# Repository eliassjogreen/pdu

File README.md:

# 10" 1U PDU

A modular 10" 1U PDU which repurposes the common slot HP server power supplies.
It's designed around a single 12V rail supplied by the powerful and probably
overkill HP common slot power supplies. To supply downstream devices there are
internal XT60 connectors, which in turn are used to buck or boost the 12V rail
to desired voltages, for example 19V for common mini-pc's.

## Specifications

Depending on the [HP common slot power supply](https://support.hpe.com/hpesc/public/docDisplay?docId=c03502743)
you decide to get there is some variation in the capabilities of the PDU. I
have the 750W (DPS-750RB and HSTNS-PL18) variant of the supply outputting 12V
62.5A on the main rail, but also 12V 2.5A of standby power which is always on.
The PDU will probably work with the 1200W version, but because I designed it
with the 750W version in mind some connectors and the PCB might technically be
undersized for such loads. The smaller 460W version should work just fine still.

There are 6 XT60 connectors on the rail for supplying different devices,
supporting 30A continuous current and 60A surge current each, which should
be more than enough for most devices (360W 12V). The main bottleneck will be
the jumper module which connects the PSU to the rail (and in the future a
backup PSU or UPS), which is currently designed arount the XT90 connector which
is "only" rated for 45A continuous current and 90A surge current which may be a
problem if you draw >540W continuously from the rail. For most homelabs this
shouldn't be any issue though, and if it is I sincerely wonder what you managed
to cram into a 10" rack?!

## Progress

Currently there's only a backplane and a simple jumper module which connects
the PSU's 12V main output to the rail, but I am planning on adding a
ideal-diode/power path controller for connecting a second power supply or
external UPS I am planning on building.

Additionally there will be USB PD modules, hopefully supporting 144W devices.
The possibilites are endless, maybe even 48V for PoE devices, but I don't
currently have any so that will have to wait.

The controller will probably (not decided yet) use a RP2040 or compatible
microcontroller with some yet-to-be-coded firmware which probably will
interface with [USB HID](https://www.usb.org/sites/default/files/pdcv11.pdf)
for power devices for interfacing with [NUT](https://networkupstools.org/).
This is still very much in the planning phase and nothing is decided yet, and
probably will be way simpler for the first revision.

## References, inspiration and links

- [jayzosayers/Common-Slot-Server-Power-Supply-Breakout-Module](https://github.com/jayzosayers/Common-Slot-Server-Power-Supply-Breakout-Module)
- [cracked-machine/CommonSlotPSU_TouchScreenController_HW](https://github.com/cracked-machine/CommonSlotPSU_TouchScreenController_HW)
- [ButtSimpleIdeas/DPS-1200-I2C](https://github.com/ButtSimpleIdeas/DPS-1200-I2C)
- [slundell/dps_charger](https://github.com/slundell/dps_charger)
- [Marx1/HP_PowerSupply_ESP8266_Breakout](https://github.com/Marx1/HP_PowerSupply_ESP8266_Breakout)
- [KCORES/KCORES-CSPS-to-ATX-Converter](https://github.com/KCORES/KCORES-CSPS-to-ATX-Converter)
- [Rob Ruark: Common Slot Breakout](http://robruark.com/projects/common_slot/common_slot.html)

## Licenses

### Hardware

All hardware including but not limited to: PCB layouts, schematics, CAD files,
BOM, gerbers, graphic designs and hardware documentation are licensed under the
CERN-OHL-S-V2 license as found [here](LICENSES/CERN-OHL-S-2.0.txt).

### Software

All software including but not limited to: firmware, scripts, configuration
files and software documentation are licensed under the GPLv3 license as found
[here](LICENSES/GPL-3.0.txt).

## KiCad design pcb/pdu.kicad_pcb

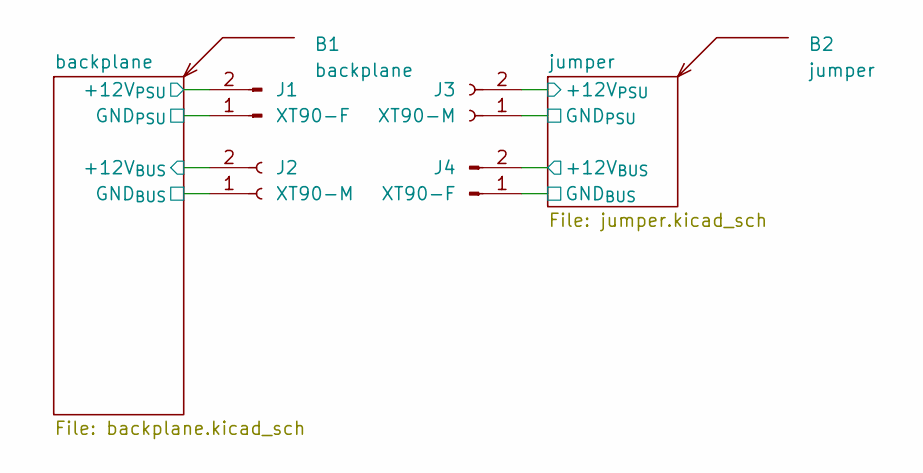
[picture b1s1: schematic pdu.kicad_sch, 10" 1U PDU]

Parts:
B1: backplane; Board
B2: jumper; Board
J1, J4: XT90-F; AMASS_XT90H-F_1x02_P11.0mm_Vertical
J2, J3: XT90-M; AMASS_XT90H-M_1x02_P11.0mm_Vertical

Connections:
/backplane/+12V_{BUS}: J2.2; also elsewhere on the board
/backplane/+12V_{PSU}: J1.2; also elsewhere on the board
/backplane/GND_{BUS}: J2.1; also elsewhere on the board
/backplane/GND_{PSU}: J1.1; also elsewhere on the board
/jumper/+12V_{BUS}: J3.2, J4.2
/jumper/GND_{BUS}: J3.1, J4.1

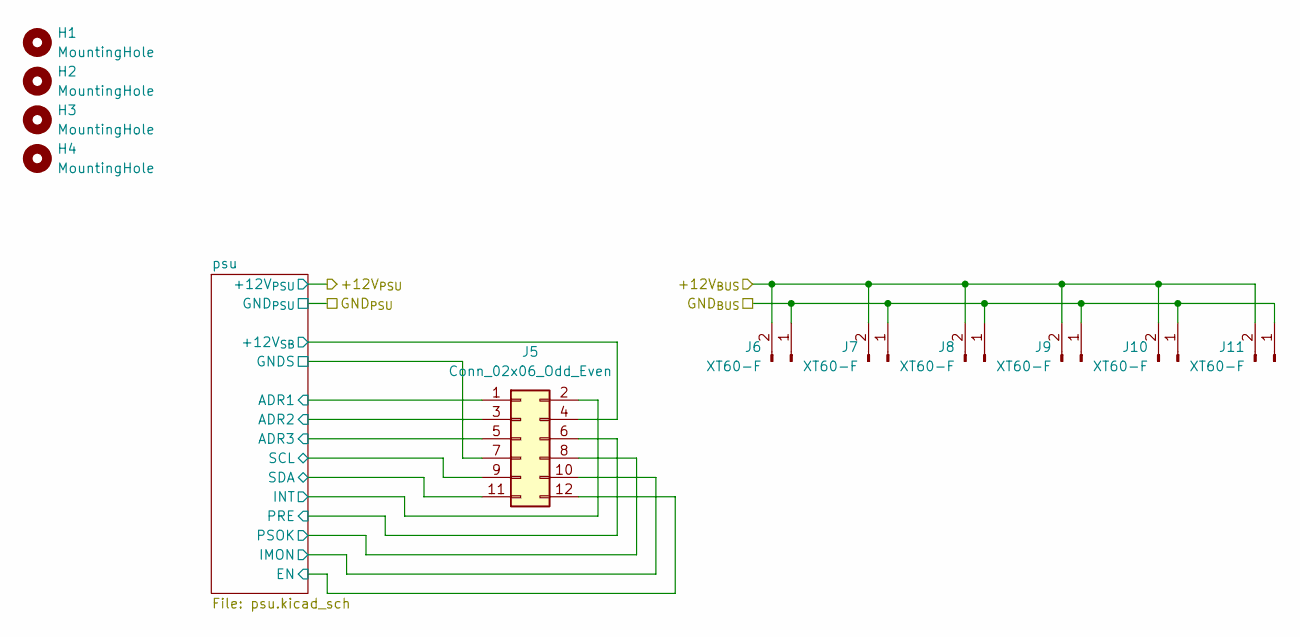
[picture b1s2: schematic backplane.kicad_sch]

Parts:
H1, H2, H3, H4: MountingHole; MountingHole_3.2mm_M3
J5: Conn_02x06_Odd_Even; PinHeader_2x06_P2.54mm_Vertical
J6, J7, J8, J9, J10, J11: XT60-F; AMASS_XT60-F_1x02_P7.20mm_Vertical

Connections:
/backplane/+12V_{BUS}: J6.2, J7.2, J8.2, J9.2, J10.2, J11.2; also elsewhere on the board
/backplane/GND_{BUS}: J6.1, J7.1, J8.1, J9.1, J10.1, J11.1; also elsewhere on the board
/backplane/psu/+12V_{SB}: J5.4; also elsewhere on the board
/backplane/psu/ADR1: J5.1; also elsewhere on the board
/backplane/psu/ADR2: J5.3; also elsewhere on the board
/backplane/psu/ADR3: J5.5; also elsewhere on the board
/backplane/psu/EN: J5.12; also elsewhere on the board
/backplane/psu/GNDS: J5.7; also elsewhere on the board
/backplane/psu/IMON: J5.10; also elsewhere on the board
/backplane/psu/INT: J5.2; also elsewhere on the board
/backplane/psu/PRE: J5.6; also elsewhere on the board
/backplane/psu/PSOK: J5.8; also elsewhere on the board
/backplane/psu/SCL: J5.9; also elsewhere on the board
/backplane/psu/SDA: J5.11; also elsewhere on the board

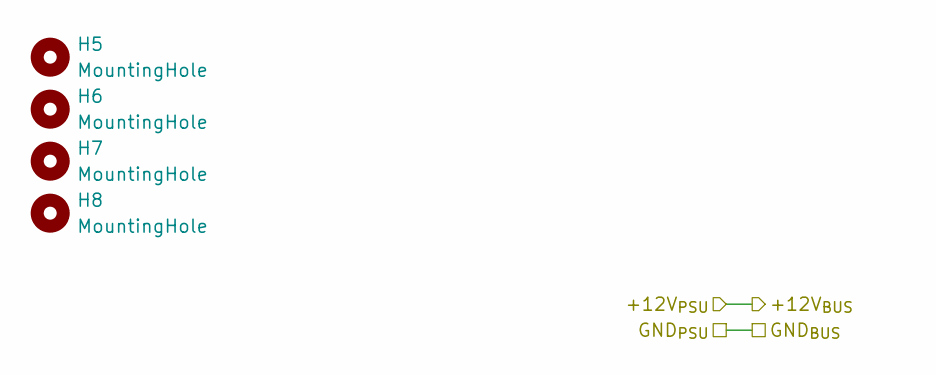
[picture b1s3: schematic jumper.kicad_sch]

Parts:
H5, H6, H7, H8: MountingHole; MountingHole_3.2mm_M3

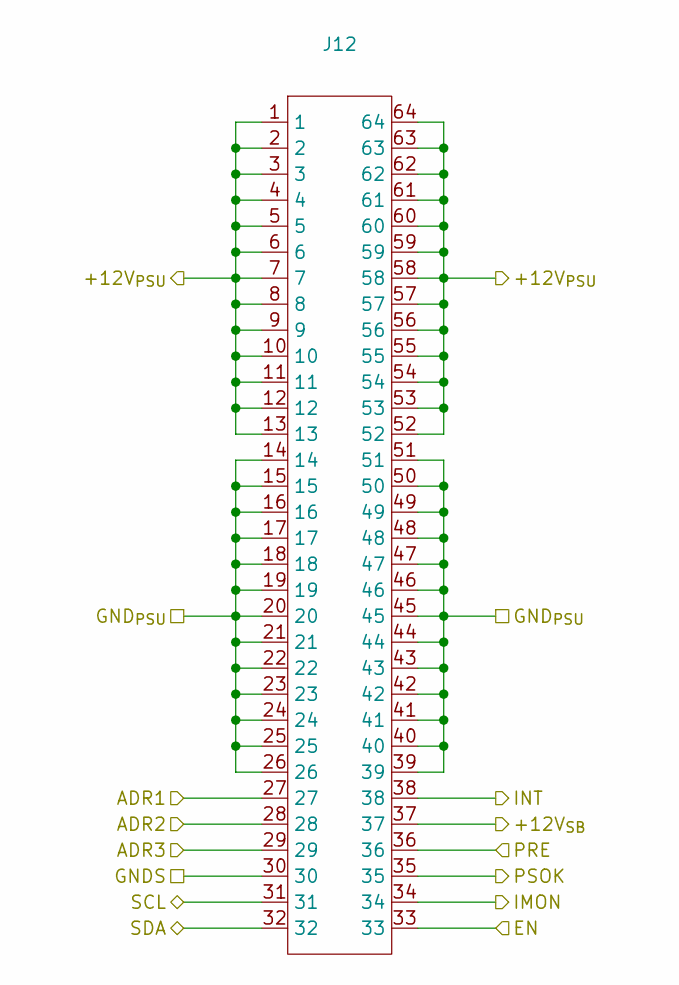
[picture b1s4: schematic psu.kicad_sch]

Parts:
J12: WingTAT_S-64M-2.54-5

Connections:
/backplane/+12V_{PSU}: J12.1, J12.2, J12.3, J12.4, J12.5, J12.6, J12.7, J12.8, J12.9, J12.10, J12.11, J12.12, J12.13, J12.52, J12.53, J12.54, J12.55, J12.56, J12.57, J12.58, J12.59, J12.60, J12.61, J12.62, J12.63, J12.64; also elsewhere on the board
/backplane/GND_{PSU}: J12.14, J12.15, J12.16, J12.17, J12.18, J12.19, J12.20, J12.21, J12.22, J12.23, J12.24, J12.25, J12.26, J12.39, J12.40, J12.41, J12.42, J12.43, J12.44, J12.45, J12.46, J12.47, J12.48, J12.49, J12.50, J12.51; also elsewhere on the board
/backplane/psu/+12V_{SB}: J12.37; also elsewhere on the board
/backplane/psu/ADR1: J12.27; also elsewhere on the board
/backplane/psu/ADR2: J12.28; also elsewhere on the board
/backplane/psu/ADR3: J12.29; also elsewhere on the board
/backplane/psu/EN: J12.33; also elsewhere on the board
/backplane/psu/GNDS: J12.30; also elsewhere on the board
/backplane/psu/IMON: J12.34; also elsewhere on the board
/backplane/psu/INT: J12.38; also elsewhere on the board
/backplane/psu/PRE: J12.36; also elsewhere on the board
/backplane/psu/PSOK: J12.35; also elsewhere on the board
/backplane/psu/SCL: J12.31; also elsewhere on the board
/backplane/psu/SDA: J12.32; also elsewhere on the board

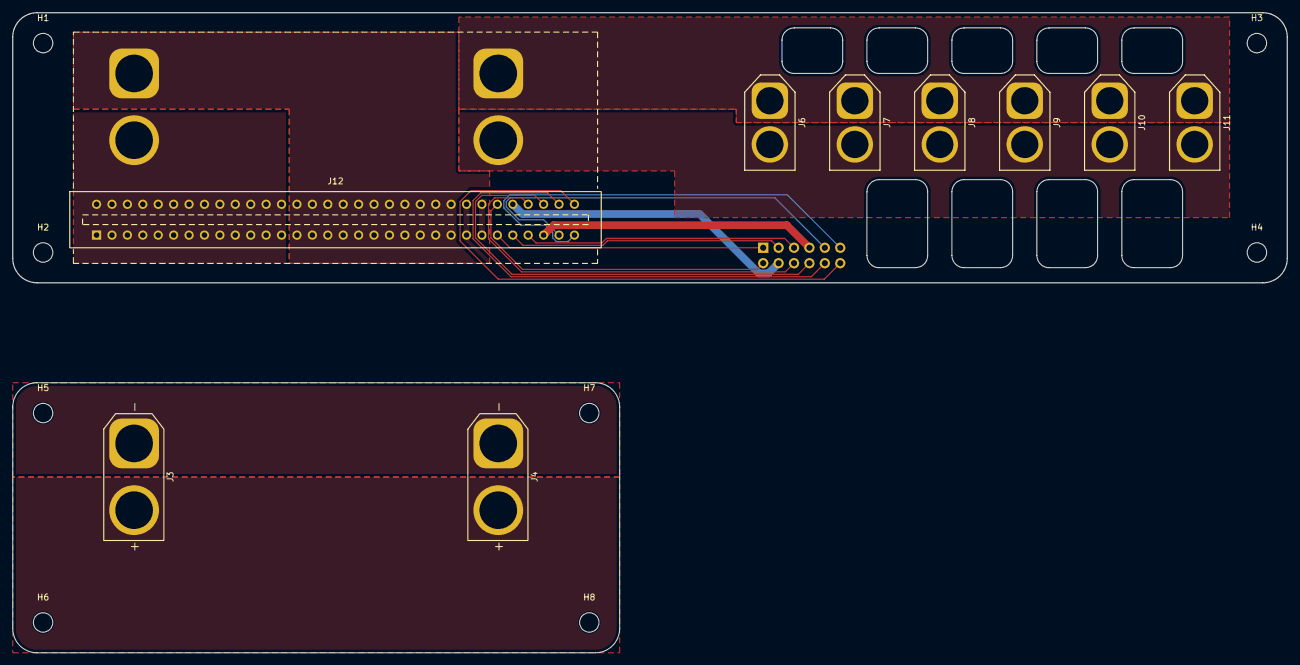
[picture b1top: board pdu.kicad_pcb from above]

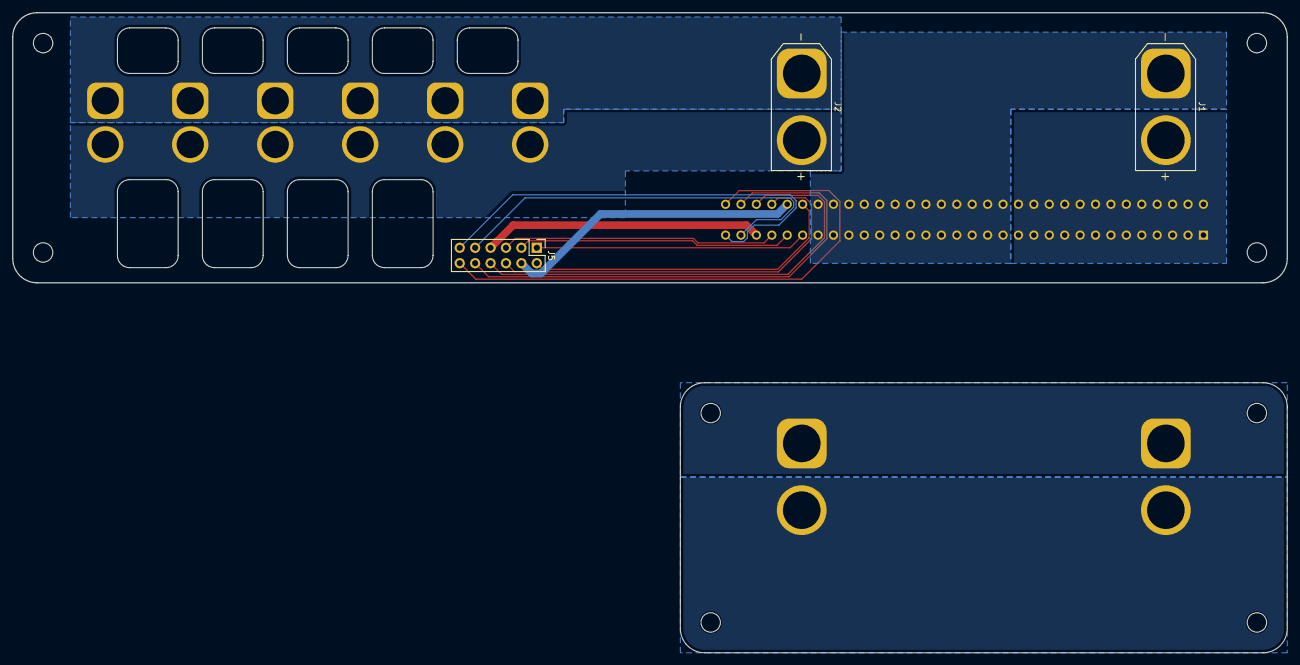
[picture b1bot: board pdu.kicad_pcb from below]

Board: 2 copper layers, 210.0 x 44.5 mm, 22 parts (3 on the bottom side), 18 nets.

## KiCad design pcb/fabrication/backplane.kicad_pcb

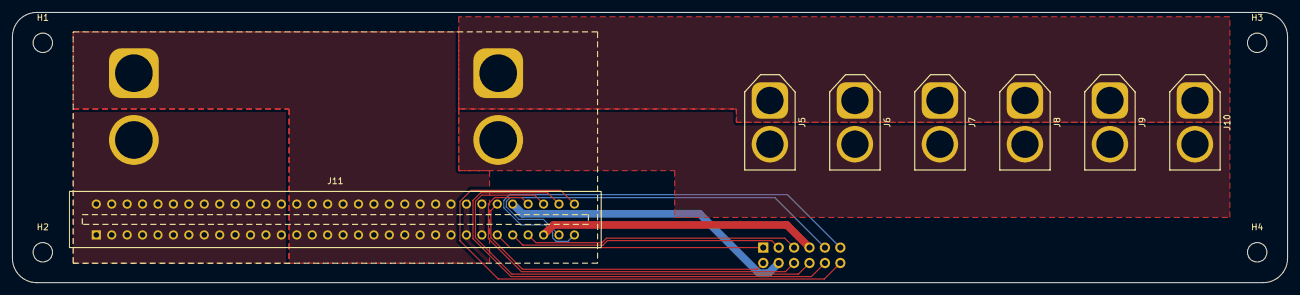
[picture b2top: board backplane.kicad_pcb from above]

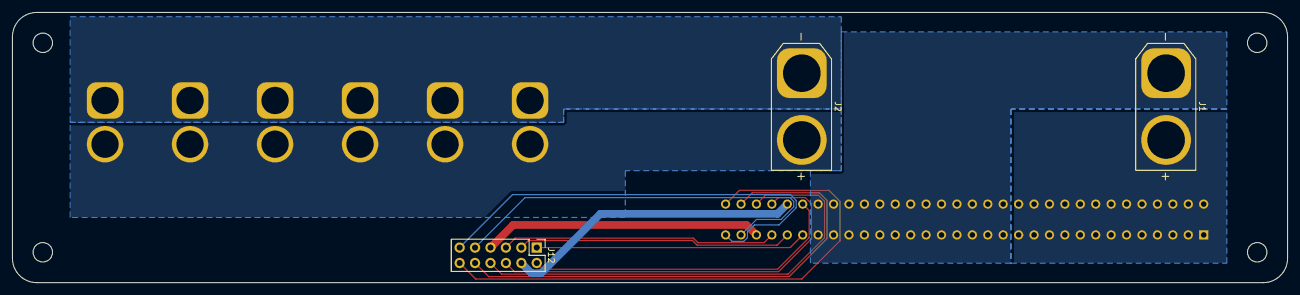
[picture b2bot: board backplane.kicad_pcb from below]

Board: 2 copper layers, 210.0 x 44.5 mm, 15 parts (3 on the bottom side), 16 nets.

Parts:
B1: backplane; Board
H1, H2, H3, H4: MountingHole; MountingHole_3.2mm_M3
J1: XT90-F; AMASS_XT90H-F_1x02_P11.0mm_Vertical
J2: XT90-M; AMASS_XT90H-M_1x02_P11.0mm_Vertical
J5, J6, J7, J8, J9, J10: XT60-F; AMASS_XT60-F_1x02_P7.20mm_Vertical
J11: WingTAT_S-64M-2.54-5
J12: Conn_02x06_Odd_Even; PinHeader_2x06_P2.54mm_Vertical

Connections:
/backplane/+12V_{BUS}: J2.2, J5.2, J6.2, J7.2, J8.2, J9.2, J10.2
/backplane/+12V_{PSU}: J1.2, J11.1, J11.2, J11.3, J11.4, J11.5, J11.6, J11.7, J11.8, J11.9, J11.10, J11.11, J11.12, J11.13, J11.52, J11.53, J11.54, J11.55, J11.56, J11.57, J11.58, J11.59, J11.60, J11.61, J11.62, J11.63, J11.64
/backplane/GND_{BUS}: J2.1, J5.1, J6.1, J7.1, J8.1, J9.1, J10.1
/backplane/GND_{PSU}: J1.1, J11.14, J11.15, J11.16, J11.17, J11.18, J11.19, J11.20, J11.21, J11.22, J11.23, J11.24, J11.25, J11.26, J11.39, J11.40, J11.41, J11.42, J11.43, J11.44, J11.45, J11.46, J11.47, J11.48, J11.49, J11.50, J11.51
/backplane/psu/+12V_{SB}: J11.37, J12.4
/backplane/psu/ADR1: J11.27, J12.1
/backplane/psu/ADR2: J11.28, J12.3
/backplane/psu/ADR3: J11.29, J12.5
/backplane/psu/EN: J11.33, J12.12
/backplane/psu/GNDS: J11.30, J12.7
/backplane/psu/IMON: J11.34, J12.10
/backplane/psu/INT: J11.38, J12.2
/backplane/psu/PRE: J11.36, J12.6
/backplane/psu/PSOK: J11.35, J12.8
/backplane/psu/SCL: J11.31, J12.9
/backplane/psu/SDA: J11.32, J12.11

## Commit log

2026-02-05 feat: Initial commit
2026-02-05 fix: Hide mounting hole references
2026-02-05 fix: Add fabrication output to gitignore
2026-02-05 chore: Reorganize 3d models
2026-02-05 feat: Expand on README
2026-02-05 fix: DRC issue
2026-02-07 feat: ERC and DRC in CI
2026-02-07 fix: ERC, mark edge connector pins as passive
2026-02-07 fix: Add phony for `all` command
2026-02-07 feat: Add make commands to separate boards
2026-02-07 feat: Add make commands to create pcbway and jlcpcb output
2026-02-07 feat: References, inspiration and links
2026-02-09 feat: Add TPS2490 hot-swap controller symbol
2026-02-09 feat: Add TPS2490 to project sym table
